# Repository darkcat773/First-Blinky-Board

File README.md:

# First-Blinky-Board

My first hardware project! Followed the Stasis(Hack Club) guide and used KiCad. The Blinky Board's LEDs map out a Cygnus(constellation).

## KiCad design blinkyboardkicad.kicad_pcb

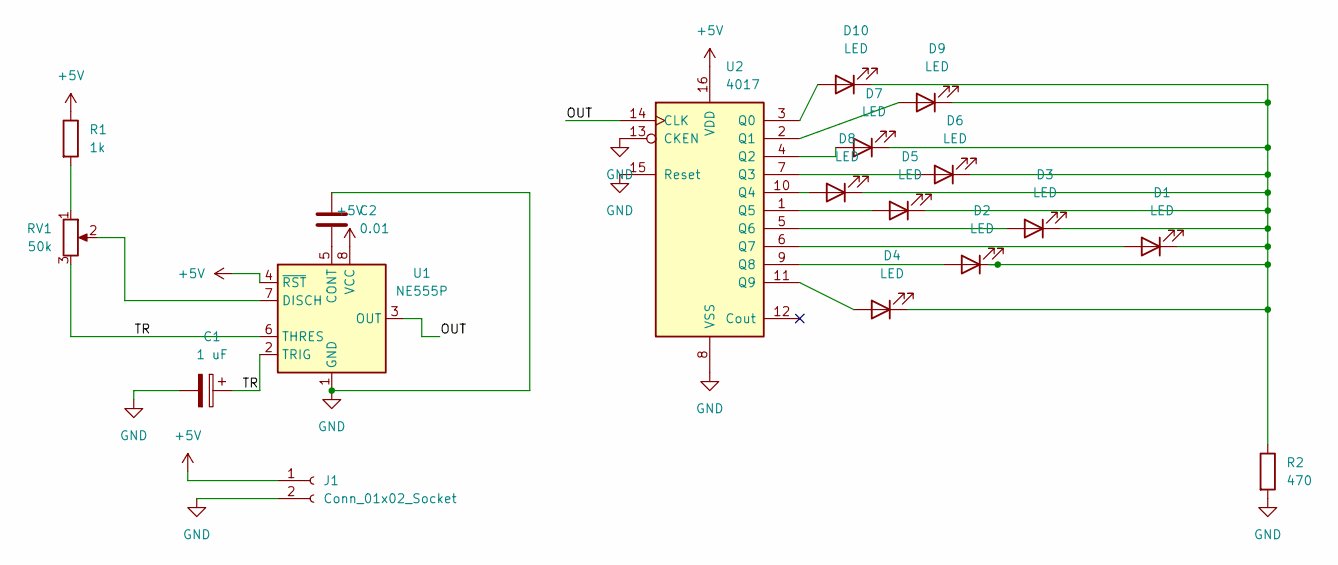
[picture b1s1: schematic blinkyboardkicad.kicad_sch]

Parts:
C1: 1 uF; CP_Radial_D5.0mm_P2.00mm
C2: 0.01; C_Disc_D7.0mm_W2.5mm_P5.00mm
D1, D2, D3, D4, D5, D6, D7, D8, D9, D10: LED; LED_D3.0mm
J1: Conn_01x02_Socket; PinHeader_1x02_P2.54mm_Vertical
R1: 1k; R_Axial_DIN0207_L6.3mm_D2.5mm_P7.62mm_Horizontal
R2: 470; R_Axial_DIN0207_L6.3mm_D2.5mm_P7.62mm_Horizontal
RV1: 50k; Potentiometer_Vishay_T93YA_Vertical
U1: NE555P; DIP-8_W7.62mm
U2: 4017; N16

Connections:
+5V: J1.1, R1.1, U1.4 (~RST), U1.8 (VCC), U2.16 (VDD)
/OUT: U1.3 (OUT), U2.14 (CLK)
/TR: C1.1, RV1.3, U1.2 (TRIG), U1.6 (THRES)
GND: C1.2, C2.1, J1.2, R2.2, U1.1 (GND), U2.8 (VSS), U2.13 (CKEN), U2.15 (Reset)
unnamed: D1.2 (A), U2.6 (Q7)
unnamed: D1.1 (K), D2.1 (K), D3.1 (K), D4.1 (K), D5.1 (K), D6.1 (K), D7.1 (K), D8.1 (K), D9.1 (K), D10.1 (K), R2.1
unnamed: D2.2 (A), U2.9 (Q8)
unnamed: D3.2 (A), U2.5 (Q6)
unnamed: D4.2 (A), U2.11 (Q9)
unnamed: D5.2 (A), U2.1 (Q5)
unnamed: D6.2 (A), U2.7 (Q3)
unnamed: D7.2 (A), U2.4 (Q2)
unnamed: D8.2 (A), U2.10 (Q4)
unnamed: D9.2 (A), U2.2 (Q1)
unnamed: D10.2 (A), U2.3 (Q0)
unnamed: R1.2, RV1.1
unnamed: C2.2, U1.5 (CONT)
unnamed: RV1.2, U1.7 (DISCH)

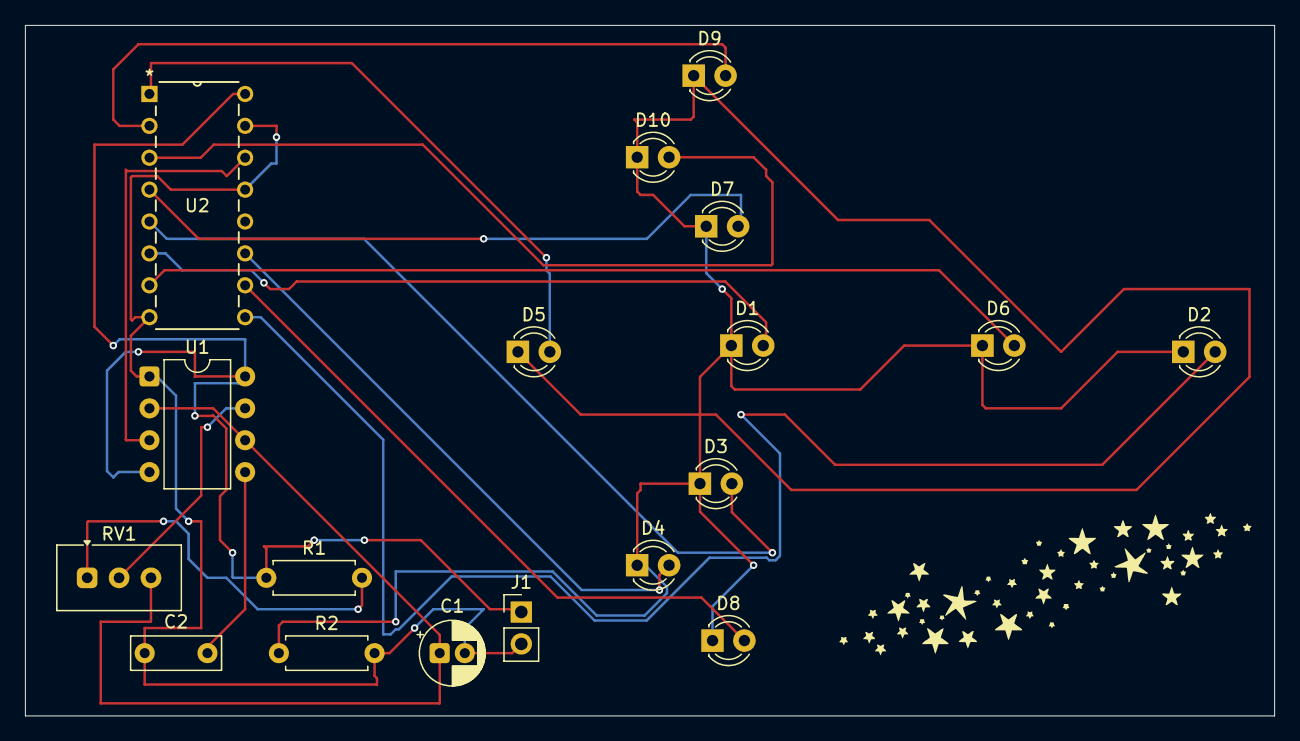
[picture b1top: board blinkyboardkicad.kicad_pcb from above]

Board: 2 copper layers, 99.5 x 55.0 mm, 18 parts (0 on the bottom side), 18 nets.

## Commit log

2026-04-13 Schematic and PCB
2026-04-13 added image to README
2026-04-13 replaced Gerber folder with zip
